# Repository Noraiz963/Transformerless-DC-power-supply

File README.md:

# Transformerless DC Power Supply

A capacitor-dropper based transformerless power supply designed in KiCad, converting AC mains input into a regulated 5V DC output without using a bulky step-down transformer.

## Circuit Overview

The design is broken into functional stages:

1. **AC voltage dropping (capacitive dropper)**: R1 (1MΩ bleeder) and C1 (2.2µF) drop the AC line voltage without a transformer, relying on the capacitor's reactance rather than resistive dissipation to minimize heat loss.
2. **AC to pulsating DC**: Full-wave bridge rectifier using 4x 1N4007 diodes (D1–D4).
3. **Filtering**: C2 (0.1µF) and C3 (1000µF) smooth the rectified output into a steadier DC level.
4. **Voltage fixing (zener clamp)**: Zener diodes D8 and D9 with R2 and R3 (20kΩ) pre-regulate the voltage before the linear regulator stage.
5. **Voltage regulation**: LM7805 (U2) fixed 5V linear regulator, producing a clean, stable 5V output.
6. **Indicator**: LED (D7) with 2.2kΩ resistor (R4) shows when the supply is powered.
7. **Noise filtering**: 470µF output capacitor (C4) to reduce ripple/noise on the final DC output.
8. **Connectors**: 3.5mm connectors for AC input (J1) and DC output (J2).

## Schematic

## PCB Layout

## 3D Render

## Bill of Materials

| Ref | Component | Value |
|-----|-----------|-------|
| R1 | Resistor | 1MΩ |
| C1 | Capacitor (dropper) | 2.2µF |
| D1–D4 | Diode | 1N4007 |
| C2 | Capacitor | 0.1µF |
| C3 | Electrolytic Capacitor | 1000µF |
| D8, D9 | Zener Diode | — |
| R2, R3 | Resistor | 20kΩ |
| R4 | Resistor | 2.2kΩ |
| D7 | LED | Power indicator |
| U2 | Voltage Regulator | LM7805 (TO-220) |
| C4 | Electrolytic Capacitor | 470µF |
| J1 | Connector (3.5mm) | AC Input |
| J2 | Connector (3.5mm) | DC Output |

## Tools Used

- KiCad 10.0 (schematic capture, PCB layout, 3D visualization)

## Status

Completed — second PCB design project, building on the AC to DC converter project with a full regulated, transformerless supply design.

## ⚠️ Safety Note

This is a **transformerless design**, meaning the circuit has a direct (non-isolated) electrical connection to the AC mains line. This is a well-known technique in low-power electronics but carries real shock hazard risk since there is no galvanic isolation from mains voltage. This project was built for learning purposes on the KiCad design workflow (schematic capture, ERC, PCB layout, DRC) — exercise caution and follow proper safety practices (fusing, enclosure, isolation) before powering or handling any physically built version of this circuit.

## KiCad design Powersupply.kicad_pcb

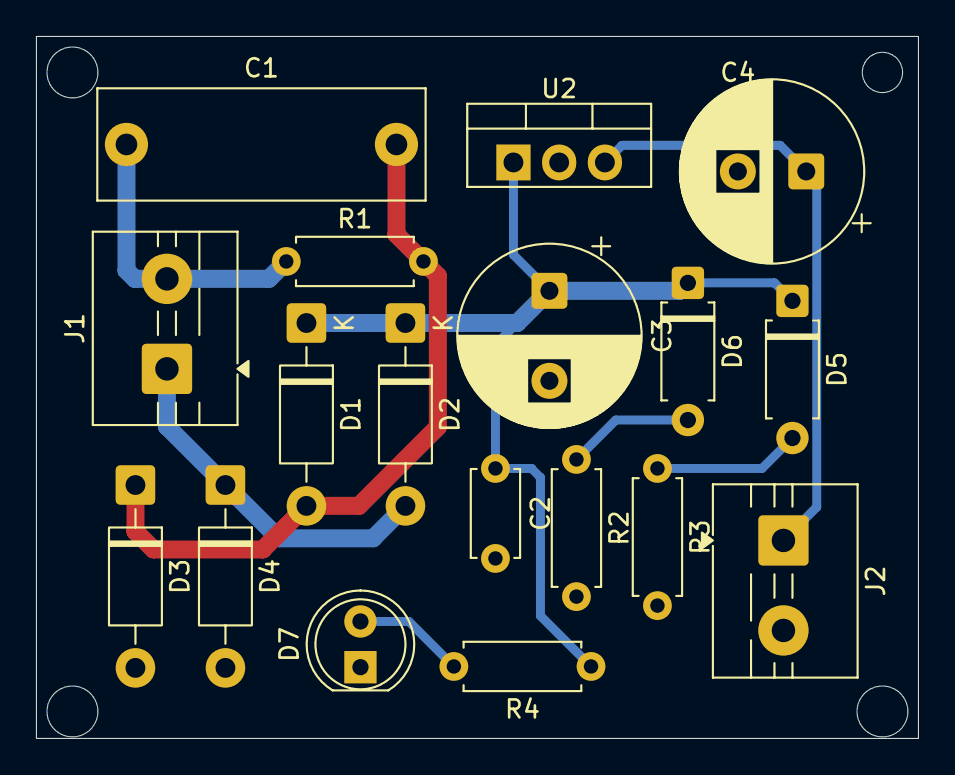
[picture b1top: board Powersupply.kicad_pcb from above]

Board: 2 copper layers, 49.0 x 39.0 mm, 18 parts (0 on the bottom side), 9 nets.

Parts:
C1: 2.2u; C_Rect_L18.0mm_W6.0mm_P15.00mm_FKS3_FKP3
C2: 0.1uf; C_Disc_D4.7mm_W2.5mm_P5.00mm
C3: 1000uf; CP_Radial_D10.0mm_P5.00mm
C4: 470uf; CP_Radial_D10.0mm_P3.80mm
D1, D2, D3, D4: 1N4007; D_DO-41_SOD81_P10.16mm_Horizontal
D5, D6: D_Zener; D_A-405_P7.62mm_Horizontal
D7: LED; LED_D5.0mm
J1, J2: 3.5mm; TerminalBlock_MaiXu_MX126-5.0-02P_1x02_P5.00mm
R1: 1M; R_Axial_DIN0207_L6.3mm_D2.5mm_P7.62mm_Horizontal
R2, R3: 20k; R_Axial_DIN0207_L6.3mm_D2.5mm_P7.62mm_Horizontal
R4: 2.2k; R_Axial_DIN0207_L6.3mm_D2.5mm_P7.62mm_Horizontal
U2: LM7805_TO220; TO-220-3_Vertical

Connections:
GND: C2.2, C3.2, C4.2, D3.2 (A), D4.2 (A), D7.1 (K), J2.2, R2.2, R3.2, U2.2 (GND)
unnamed: C1.2, D1.2 (A), D3.1 (K), R1.2
unnamed: C2.1, C3.1, D1.1 (K), D2.1 (K), D5.1 (K), D6.1 (K), R4.1, U2.1 (VI)
unnamed: D2.2 (A), D4.1 (K), J1.1
unnamed: D7.2 (A), R4.2
unnamed: D6.2 (A), R2.1
unnamed: D5.2 (A), R3.1
unnamed: C1.1, J1.2, R1.1
unnamed: C4.1, J2.1, U2.3 (VO)
